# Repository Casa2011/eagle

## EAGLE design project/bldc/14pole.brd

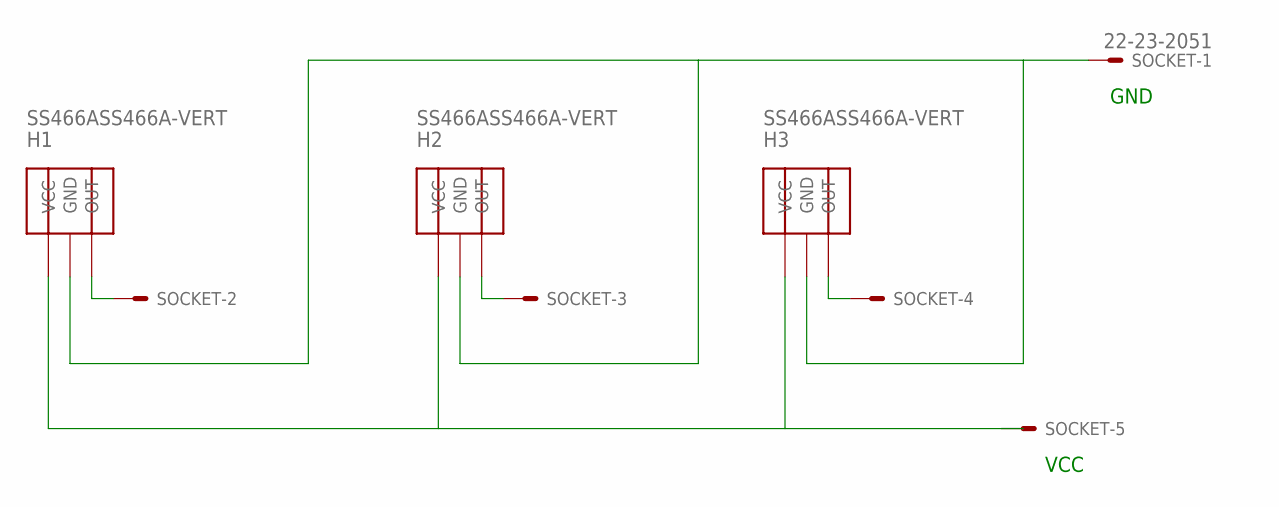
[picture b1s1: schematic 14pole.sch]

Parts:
H1, H2, H3: SS466ASS466A-VERT; SS466A
SOCKET: 22-23-2051

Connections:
unnamed: H1.GND, H2.GND, H3.GND, SOCKET.1
unnamed: H1.VCC, H2.VCC, H3.VCC, SOCKET.5
unnamed: H3.OUT, SOCKET.4
unnamed: H2.OUT, SOCKET.3
unnamed: H1.OUT, SOCKET.2

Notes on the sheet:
VCC
GND

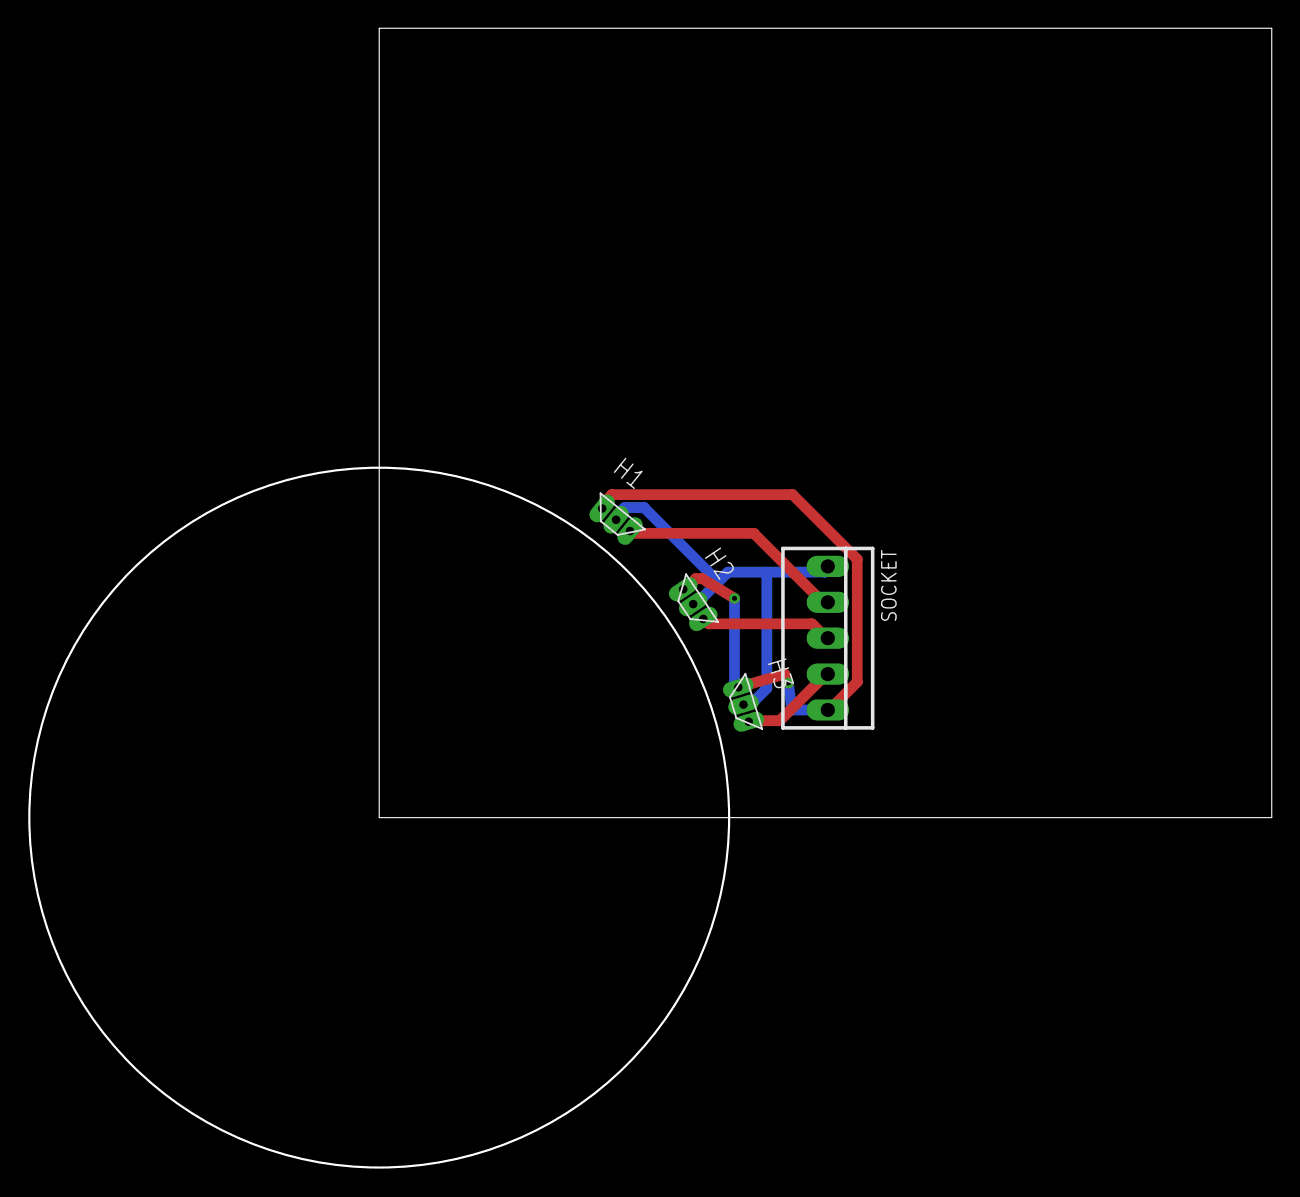
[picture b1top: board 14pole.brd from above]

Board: 2 copper layers, 87.9 x 80.6 mm, 4 parts (0 on the bottom side), 5 nets.

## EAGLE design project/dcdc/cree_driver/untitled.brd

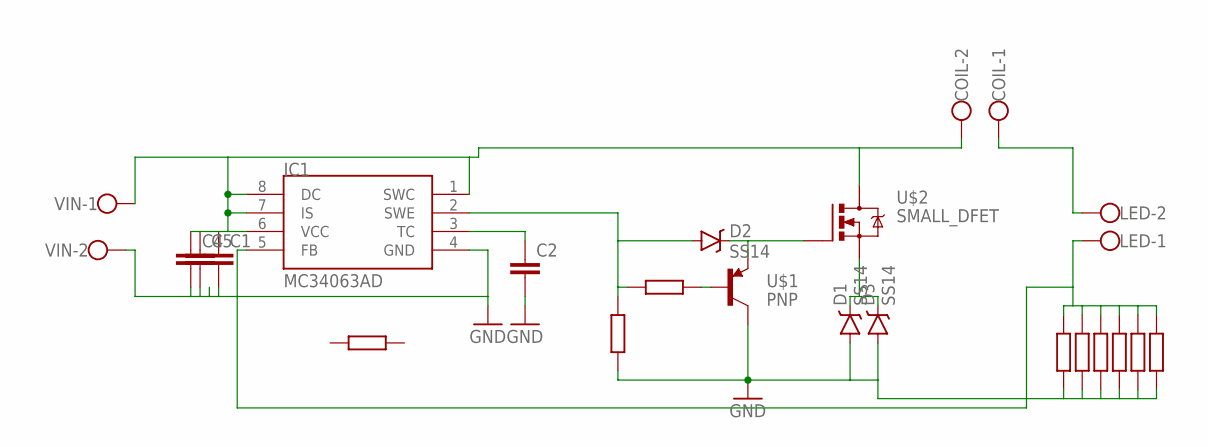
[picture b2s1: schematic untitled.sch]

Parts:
C1, C4, C5: CC0805; C0805
C2: CC0603; C0603
COIL: W237-102
D1, D2, D3: SS14; SMA-DIODE
IC1: MC34063AD; SOIC8
LED: W237-102
R1: R1206
R3, R4, R5, R6, R7, R8, R9, R10: R0805
U$1: PNP; SOT23
U$2: SMALL_DFET; SMALL_DIRFET
VIN: W237-102

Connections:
GND: C1.2, C2.2, C4.2, C5.2, D1.A, D3.A, IC1.4 (GND), R4.1, R5.1, R6.1, R7.1, R8.1, R9.1, R10.1, U$1.3 (C), VIN.2
unnamed: C1.1, C4.1, C5.1, COIL.2, IC1.1 (SWC), IC1.6 (VCC), IC1.7 (IS), IC1.8 (DC), U$2.D, U$2.D` (D), VIN.1
unnamed: C2.1, IC1.3 (TC)
unnamed: D2.C, U$1.2 (E), U$2.G
unnamed: R3.2, U$1.1 (B)
unnamed: D2.A, IC1.2 (SWE), R3.1, R4.2
unnamed: D1.C, D3.C, U$2.S
unnamed: COIL.1, LED.2
unnamed: IC1.5 (FB), LED.1, R5.2, R6.2, R7.2, R8.2, R9.2, R10.2

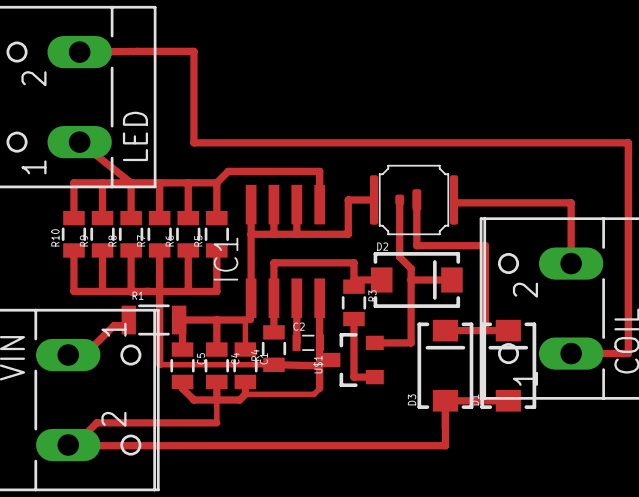
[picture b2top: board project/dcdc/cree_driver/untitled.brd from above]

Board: 2 copper layers, 22 parts (0 on the bottom side), 9 nets.

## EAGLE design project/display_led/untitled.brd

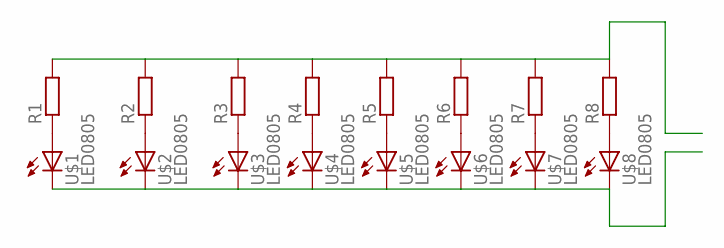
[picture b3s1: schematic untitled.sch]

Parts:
R1, R2, R3, R4, R5, R6, R7, R8: R0603; 0603
U$1, U$2, U$3, U$4, U$5, U$6, U$7, U$8: LED0805; 0805-LED

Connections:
unnamed: R1.1, U$1.A
unnamed: R2.1, U$2.A
unnamed: R3.1, U$3.A
unnamed: R4.1, U$4.A
unnamed: R5.1, U$5.A
unnamed: R6.1, U$6.A
unnamed: R7.1, U$7.A
unnamed: R8.1, U$8.A
unnamed: R1.2, R2.2, R3.2, R4.2, R5.2, R6.2, R7.2, R8.2
unnamed: U$1.C, U$2.C, U$3.C, U$4.C, U$5.C, U$6.C, U$7.C, U$8.C

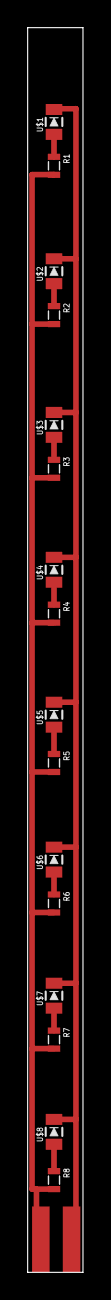
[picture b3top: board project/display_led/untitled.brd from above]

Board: 2 copper layers, 4.0 x 90.0 mm, 16 parts (0 on the bottom side), 10 nets.

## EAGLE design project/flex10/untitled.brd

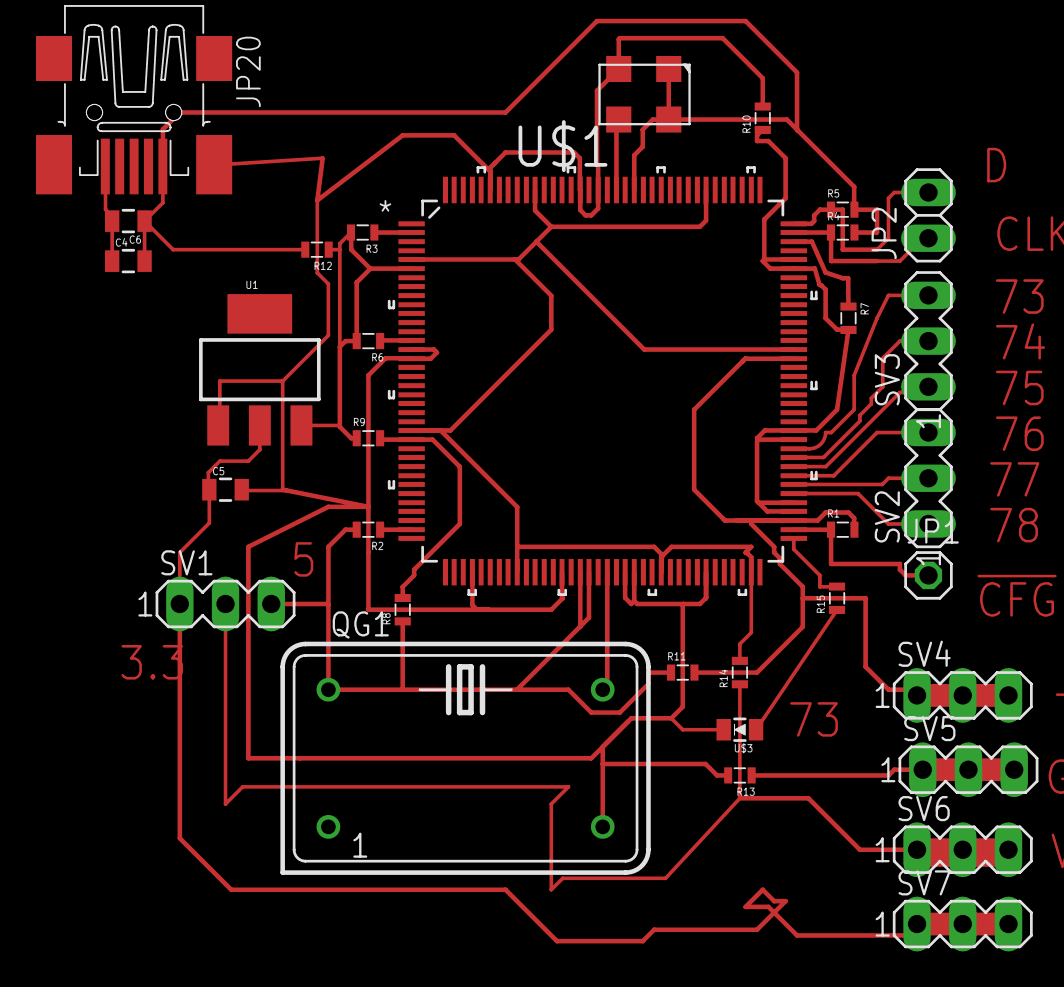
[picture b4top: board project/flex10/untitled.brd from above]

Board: 2 copper layers, 33 parts (0 on the bottom side), 21 nets.

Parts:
C4, C5, C6: C0805
JP1: 1X01
JP2: 1X02
JP20: MINI_USB.; 32005-201
QG1: DIL14S
R1, R2, R3, R4, R5, R6, R7, R8, R9, R10, R11, R12, R13, R14, R15: 0603
SV1, SV2, SV3, SV4, SV5, SV6, SV7: MA03-1
U1: SOT223
U$1: EPF10K10TI144-4N; QFP50P2200X2200X160-144N
U$2: TXC-BA*; 7X5
U$3: LED0805; 0805-LED

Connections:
!CE: R7.1, U$1.106
!CONFIG: R1.1, U$1.74
!STATUS: R2.1, U$1.35
+3V3: C5.1, SV1.1, U1.2, U1.4
CFG_DONE: R3.1, U$1.2
CLK1: U$1.125, U$2.OUT
CLK2: QG1.8, U$1.55
DATA: R5.1, U$1.108
DCLK: R4.1, U$1.107
GND: C4.1, C5.2, C6.2, JP20.GND, JP20.M1, JP20.M2, JP20.M3, JP20.M4, QG1.7, R7.2, U1.1, U$1.15, U$1.16, U$1.40, U$1.50, U$1.57, U$1.58, U$1.66, U$1.76, U$1.77, U$1.84, U$1.85, U$1.103, U$1.104, U$1.127, U$1.129, U$1.139, U$2.GND, U$3.C
IDONE: R6.1, U$1.14
unnamed: SV2.1, U$1.78
unnamed: SV2.2, U$1.79
unnamed: SV2.3, U$1.80
unnamed: SV3.1, U$1.81
unnamed: SV3.2, U$1.82
unnamed: SV3.3, U$1.83
unnamed: R15.2, U$1.73
unnamed: R15.1, U$3.A
VCC: C4.2, C6.1, JP20.VCC, QG1.14, R1.2, R2.2, R3.2, R4.2, R5.2, R6.2, R8.1, R8.2, SV1.3, U1.3, U$1.6, U$1.25, U$1.52, U$1.53, U$1.75, U$1.93, U$1.123, U$2.EN, U$2.VCC
VCCIO: SV1.2, U$1.5, U$1.24, U$1.45, U$1.61, U$1.71, U$1.94, U$1.115, U$1.134

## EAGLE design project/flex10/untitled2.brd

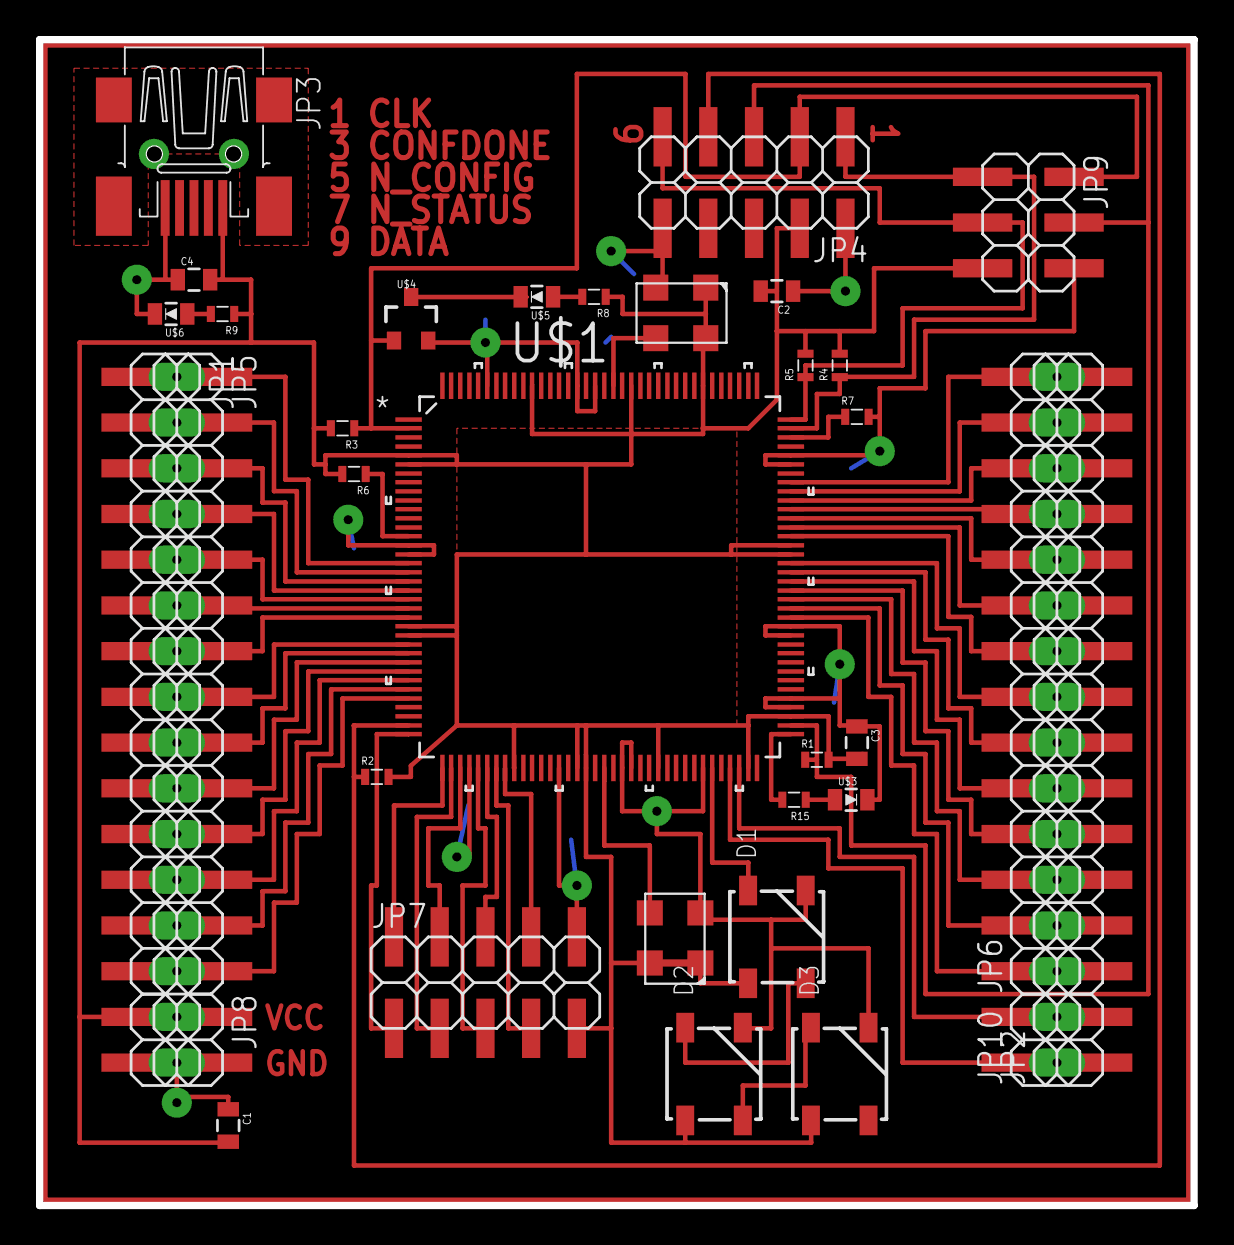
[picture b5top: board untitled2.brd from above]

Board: 2 copper layers, 64.1 x 64.8 mm, 34 parts (0 on the bottom side), 57 nets.

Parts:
C1, C2, C3, C4: C0805
D1, D2, D3: WS2812B
JP1, JP2: 1X16
JP3: MINI_USB.; 32005-201
JP4, JP7: 2X05SMD
JP5, JP6: 2X14SMD
JP8, JP10: 2X02SMD
JP9: 2X03SMD
R1, R2, R3, R4, R5, R6, R7, R8, R9, R15: 0603
U$1: EPF10K10TI144-4N; QFP50P2200X2200X160-144N
U$2, U$7: TXC-BA*; 7X5
U$3, U$5, U$6: LED0805; 0805-LED
U$4: 2N7002; SOT23

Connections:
!CE: R7.1, U$1.106
!CONFIG: JP4.5, JP9.4, R1.1, U$1.74
!STATUS: JP4.7, R2.1, U$1.35
CFG_DONE: JP4.3, JP9.2, R3.1, U$1.2, U$4.1
CLK1: U$1.125, U$2.OUT
CLK2: U$1.55, U$7.OUT
D1: JP7.1, U$1.36
D2: JP7.2, U$1.37
D3: JP7.3, U$1.38
D4: JP7.4, U$1.39
D5: JP7.5, U$1.41
D6: JP7.6, U$1.42
D7: JP7.7, U$1.43
D8: JP7.8, U$1.44
D9: JP2.1, JP10.1, JP10.2, U$1.69
D10: JP2.2, JP10.3, JP10.4, U$1.70
DATA: JP4.9, JP9.3, R5.1, U$1.108
DCLK: JP4.1, JP9.1, R4.1, U$1.107
GND: C1.1, C2.1, C3.1, C4.1, D1.3, D2.3, D3.3, JP1.16, JP3.GND, JP3.M1, JP3.M2, JP3.M3, JP3.M4, JP4.2, JP4.10, JP7.10, JP8.3, JP8.4, JP9.6, R7.2, U$1.15, U$1.16, U$1.40, U$1.50, U$1.57, U$1.58, U$1.66, U$1.76, U$1.77, U$1.84, U$1.85, U$1.103, U$1.104, U$1.127, U$1.129, U$1.139, U$2.GND, U$3.C, U$4.2, U$6.C, U$7.GND
IDONE: R6.1, U$1.14
LED_DIN: D1.4, U$1.67
unnamed: JP2.11, JP6.17, JP6.18, U$1.96
unnamed: JP2.12, JP6.19, JP6.20, U$1.97
unnamed: JP1.1, JP5.1, JP5.2, U$1.17
unnamed: JP1.2, JP5.3, JP5.4, U$1.18
unnamed: R15.2, U$1.73
unnamed: R15.1, U$3.A
unnamed: JP2.13, JP6.21, JP6.22, U$1.98
unnamed: JP1.3, JP5.5, JP5.6, U$1.19
unnamed: JP1.4, JP5.7, JP5.8, U$1.20
unnamed: JP1.5, JP5.9, JP5.10, U$1.21
unnamed: JP1.6, JP5.11, JP5.12, U$1.22
unnamed: JP1.7, JP5.13, JP5.14, U$1.23
unnamed: JP1.8, JP5.15, JP5.16, U$1.26
unnamed: JP1.9, JP5.17, JP5.18, U$1.27
unnamed: JP1.10, JP5.19, JP5.20, U$1.28
unnamed: JP1.11, JP5.21, JP5.22, U$1.29
unnamed: JP1.12, JP5.23, JP5.24, U$1.30
unnamed: JP1.13, JP5.25, JP5.26, U$1.31
unnamed: JP1.14, JP5.27, JP5.28, U$1.32
unnamed: R9.2, U$6.A
unnamed: U$4.3, U$5.C
unnamed: R8.2, U$5.A
unnamed: D1.2, D2.4
unnamed: D2.2, D3.4
unnamed: JP2.14, JP6.23, JP6.24, U$1.99
unnamed: JP2.15, JP6.25, JP6.26, U$1.100
unnamed: JP2.16, JP6.27, JP6.28, U$1.101
unnamed: JP2.3, JP6.1, JP6.2, U$1.86
unnamed: JP2.4, JP6.3, JP6.4, U$1.87
unnamed: JP2.5, JP6.5, JP6.6, U$1.88
unnamed: JP2.6, JP6.7, JP6.8, U$1.89
unnamed: JP2.7, JP6.9, JP6.10, U$1.90
unnamed: JP2.8, JP6.11, JP6.12, U$1.91
unnamed: JP2.9, JP6.13, JP6.14, U$1.92
unnamed: JP2.10, JP6.15, JP6.16, U$1.95
VCC: C1.2, C2.2, C3.2, C4.2, D1.1, D2.1, D3.1, JP1.15, JP3.VCC, JP4.4, JP7.9, JP8.1, JP8.2, JP9.5, R1.2, R2.2, R3.2, R4.2, R5.2, R6.2, R8.1, R9.1, U$1.5, U$1.6, U$1.24, U$1.25, U$1.45, U$1.52, U$1.53, U$1.61, U$1.71, U$1.75, U$1.93, U$1.94, U$1.115, U$1.123, U$1.134, U$2.EN, U$2.VCC, U$7.EN, U$7.VCC

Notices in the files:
parts and their libraries:
SparkFun-FreqCtrl: Licensing: Creative Commons ShareAlike 4.0 International - https://creativecommons.org/licenses/by-sa/4.0
